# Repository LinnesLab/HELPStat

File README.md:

# HELPStat
Repository for our Handheld, EIS-Enabled, Low-cost and Portable (HELP) Potentiostat.

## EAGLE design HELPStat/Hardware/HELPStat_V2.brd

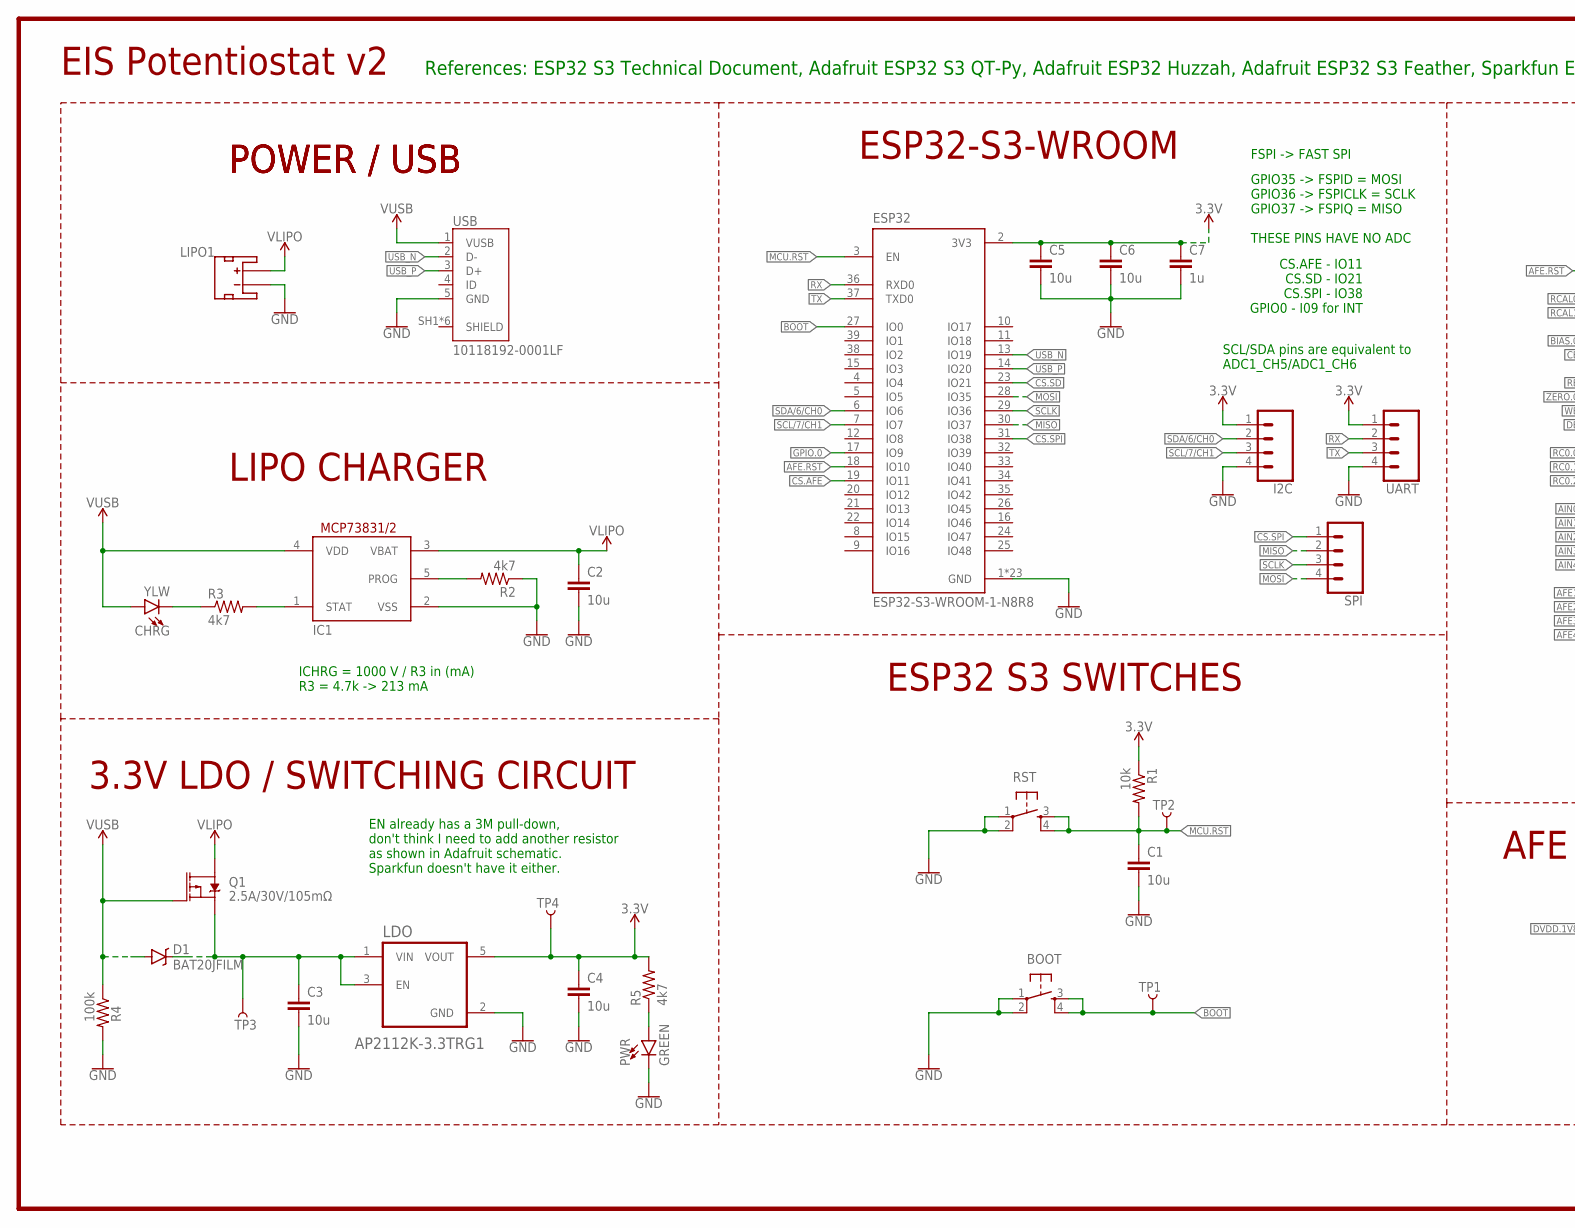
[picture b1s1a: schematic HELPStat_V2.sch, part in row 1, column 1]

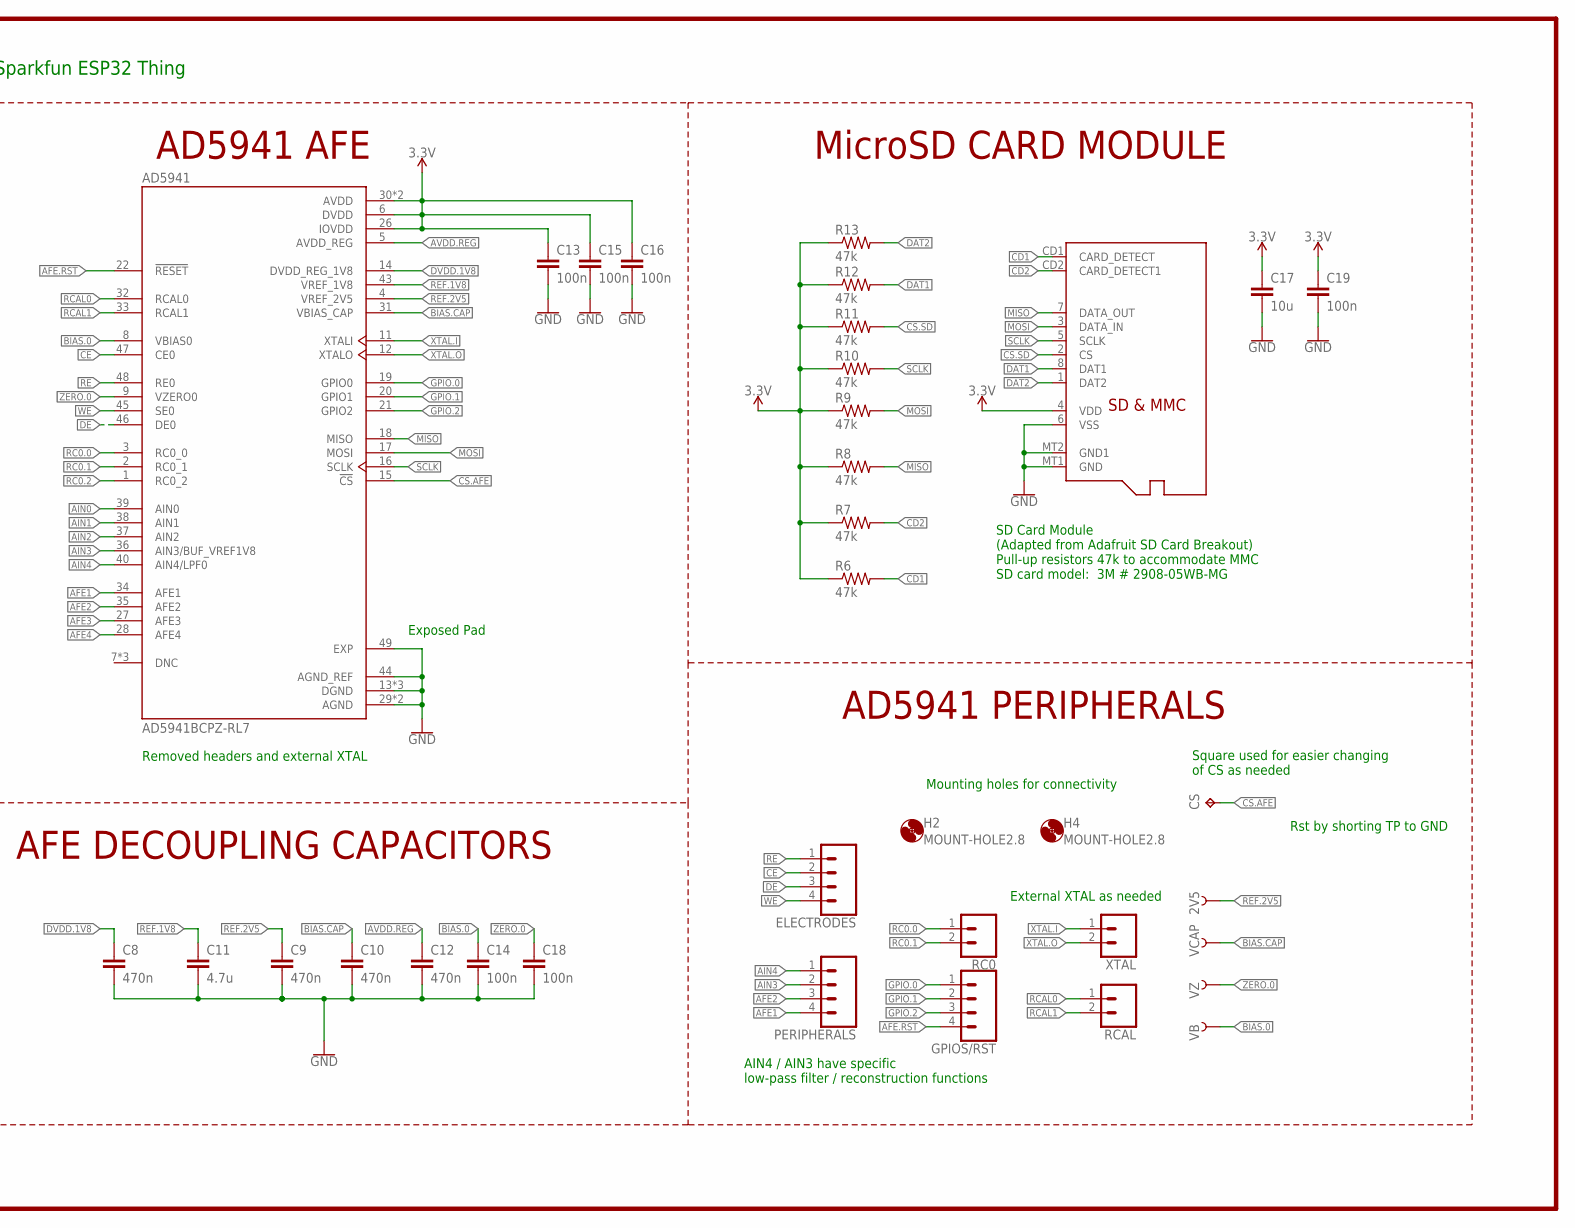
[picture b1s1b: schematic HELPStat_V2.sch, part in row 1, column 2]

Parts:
2V5: TEST-POINT3X5; PAD.03X.05
AD5941: AD5941BCPZ-RL7; QFN50P700X700X80-49N
BOOT: SPST-PTS830GG140; BUTTON-GULLWING
C1, C2, C3, C4, C5, C6, C17: 10u; C0402
C7: 1u; C0402
C8, C9, C10, C12: 470n; C0402
C11: 4.7u; C0402
C13, C14, C15, C16, C18, C19: 100n; C0402
CHRG: YLW; LED-0603
CS: TPTP20SQ; TP20SQ
D1: BAT20JFILM; SOD-323
ELECTRODES: CONN_04; 1X04
ESP32: ESP32-S3-WROOM-1-N8R8; XCVR_ESP32S3WROOM1N8R8
GPIOS/RST: CONN_041.27MM; 1X04_1.27MM
H2, H4: MOUNT-HOLE2.8; 2,8
I2C: CONN_04; 1X04
IC1: MCP73831/OT; SOT23-5L
LDO: AP2112K-3.3TRG1; SOT95P285X140-5N
LIPO1: JST_2MM_MALE; JST-2-SMD
PERIPHERALS: CONN_041.27MM; 1X04_1.27MM
PWR: GREEN; LED-0603
Q1: 2.5A/30V/105mΩ; SOT23-3
R1: 10k; R0402
R2, R3, R5: 4k7; R0402
R4: 100k; R0603
R6, R7, R8, R9, R10, R11, R12, R13: 47k; R0402
RC0: CONN_02.50MIL; 1X02_1.27MM
RCAL: CONN_02; 1X02
RST: SPST-PTS830GG140; BUTTON-GULLWING
SDCARD: MICROSD
SPI: CONN_04; 1X04
TP1, TP2, TP3, TP4: TEST-POINT3X5; PAD.03X.05
UART: CONN_04; 1X04
USB: 10118192-0001LF; AMPHENOL_10118192-0001LF
VB: TEST-POINT3X5; PAD.03X.05
VCAP: TEST-POINT3X5; PAD.03X.05
VZ: TEST-POINT3X5; PAD.03X.05
XTAL: CONN_02.50MIL; 1X02_1.27MM

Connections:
3.3V: AD5941.6 (DVDD), AD5941.26 (IOVDD), AD5941.30 (AVDD), AD5941.41 (AVDD), C4.1, C5.1, C6.1, C7.1, C13.1, C15.1, C16.1, C17.1, C19.1, ESP32.2 (3V3), I2C.1, LDO.5 (VOUT), R1.1, R5.2, R6.1, R7.1, R8.1, R9.1, R10.1, R11.1, R12.1, R13.1, SDCARD.4 (VDD), TP4.P$1, UART.1
AFE1: AD5941.34 (AFE1), PERIPHERALS.4
AFE2: AD5941.35 (AFE2), PERIPHERALS.3
AFE3: AD5941.27 (AFE3)
AFE4: AD5941.28 (AFE4)
AFE.RST: AD5941.22 (!RESET), ESP32.18 (IO10), GPIOS/RST.4
AIN0: AD5941.39 (AIN0)
AIN1: AD5941.38 (AIN1)
AIN2: AD5941.37 (AIN2)
AIN3: AD5941.36 (AIN3/BUF_VREF1V8), PERIPHERALS.2
AIN4: AD5941.40 (AIN4/LPF0), PERIPHERALS.1
AVDD.REG: AD5941.5 (AVDD_REG), C12.1
BIAS.0: AD5941.8 (VBIAS0), C14.1, VB.P$1
BIAS.CAP: AD5941.31 (VBIAS_CAP), C10.1, VCAP.P$1
BOOT: BOOT.3, BOOT.4, ESP32.27 (IO0), TP1.P$1
CD1: R6.2, SDCARD.CD1 (CARD_DETECT)
CD2: R7.2, SDCARD.CD2 (CARD_DETECT1)
CE: AD5941.47 (CE0), ELECTRODES.2
CS.AFE: AD5941.15 (!CS), CS.TP, ESP32.19 (IO11)
CS.SD: ESP32.23 (IO21), R11.2, SDCARD.2 (CS)
CS.SPI: ESP32.31 (IO38), SPI.1
DAT1: R12.2, SDCARD.8 (DAT1)
DAT2: R13.2, SDCARD.1 (DAT2)
DE: AD5941.46 (DE0), ELECTRODES.3
DVDD.1V8: AD5941.14 (DVDD_REG_1V8), C8.1
GND: AD5941.13 (DGND), AD5941.23 (DGND), AD5941.25 (DGND), AD5941.29 (AGND), AD5941.42 (AGND), AD5941.44 (AGND_REF), AD5941.49 (EXP), BOOT.1, BOOT.2, C1.2, C2.2, C3.2, C4.2, C5.2, C6.2, C7.2, C8.2, C9.2, C10.2, C11.2, C12.2, C13.2, C14.2, C15.2, C16.2, C17.2, C18.2, C19.2, ESP32.1 (GND), ESP32.40 (GND), ESP32.41_1 (GND), ESP32.41_2 (GND), ESP32.41_3 (GND), ESP32.41_4 (GND), ESP32.41_5 (GND), ESP32.41_6 (GND), ESP32.41_7 (GND), ESP32.41_8 (GND), ESP32.41_9 (GND), ESP32.41_10 (GND), ESP32.41_11 (GND), ESP32.41_12 (GND), ESP32.41_13 (GND), ESP32.41_14 (GND), ESP32.41_15 (GND), ESP32.41_16 (GND), ESP32.41_17 (GND), ESP32.41_18 (GND), ESP32.41_19 (GND), ESP32.41_20 (GND), ESP32.41_21 (GND), I2C.4, IC1.2 (VSS), LDO.2 (GND), LIPO1.1 (-), PWR.C, R2.1, R4.2, RST.1, RST.2, SDCARD.6 (VSS), SDCARD.MT1 (GND), SDCARD.MT2 (GND1), UART.4, USB.5 (GND)
GPIO.0: AD5941.19 (GPIO0), ESP32.17 (IO9), GPIOS/RST.1
GPIO.1: AD5941.20 (GPIO1), GPIOS/RST.2
GPIO.2: AD5941.21 (GPIO2), GPIOS/RST.3
MCU.RST: C1.1, ESP32.3 (EN), R1.2, RST.3, RST.4, TP2.P$1
MISO: AD5941.18 (MISO), ESP32.30 (IO37), R8.2, SDCARD.7 (DATA_OUT), SPI.2
MOSI: AD5941.17 (MOSI), ESP32.28 (IO35), R9.2, SDCARD.3 (DATA_IN), SPI.4
unnamed: CHRG.C, R3.1
unnamed: IC1.1 (STAT), R3.2
unnamed: IC1.5 (PROG), R2.2
unnamed: PWR.A, R5.1
unnamed: C3.1, D1.C, LDO.1 (VIN), LDO.3 (EN), Q1.2 (S), TP3.P$1
RC0.0: AD5941.3 (RC0_0), RC0.1
RC0.1: AD5941.2 (RC0_1), RC0.2
RC0.2: AD5941.1 (RC0_2)
RCAL0: AD5941.32 (RCAL0), RCAL.1
RCAL1: AD5941.33 (RCAL1), RCAL.2
RE: AD5941.48 (RE0), ELECTRODES.1
REF.1V8: AD5941.43 (VREF_1V8), C11.1
REF.2V5: 2V5.P$1, AD5941.4 (VREF_2V5), C9.1
RX: ESP32.36 (RXD0), UART.2
SCL/7/CH1: ESP32.7 (IO7), I2C.3
SCLK: AD5941.16 (SCLK), ESP32.29 (IO36), R10.2, SDCARD.5 (SCLK), SPI.3
SDA/6/CH0: ESP32.6 (IO6), I2C.2
TX: ESP32.37 (TXD0), UART.3
USB_N: ESP32.13 (IO19), USB.2 (D-)
USB_P: ESP32.14 (IO20), USB.3 (D+)
VLIPO: C2.1, IC1.3 (VBAT), LIPO1.2 (+), Q1.3 (D)
V_USB: CHRG.A, D1.A, IC1.4 (VDD), Q1.1 (G), R4.1, USB.1 (VUSB)
WE: AD5941.45 (SE0), ELECTRODES.4
XTAL.I: AD5941.11 (XTALI), XTAL.1
XTAL.O: AD5941.12 (XTALO), XTAL.2
ZERO.0: AD5941.9 (VZERO0), C18.1, VZ.P$1

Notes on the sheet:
ICHRG = 1000 V / R3 in (mA) R3 = 4.7k -> 213 mA
POWER / USB
LIPO CHARGER
3.3V LDO / SWITCHING CIRCUIT
ESP32 S3 SWITCHES
EIS Potentiostat v2
SCL/SDA pins are equivalent to ADC1_CH5/ADC1_CH6
References: ESP32 S3 Technical Document, Adafruit ESP32 S3 QT-Py, Adafruit ESP32 Huzzah, Adafruit ESP32 S3 Feather, Sparkfun ESP32 Thing
EN already has a 3M pull-down, don't think I need to add another resistor as shown in Adafruit schematic. Sparkfun doesn't have it either.
GPIO35 -> FSPID = MOSI GPIO36 -> FSPICLK = SCLK GPIO37 -> FSPIQ = MISO THESE PINS HAVE NO ADC
FSPI -> FAST SPI
ESP32-S3-WROOM
Exposed Pad
AFE DECOUPLING CAPACITORS
AD5941 AFE
Removed headers and external XTAL
CS.AFE - IO11 CS.SD - IO21 CS.SPI - IO38 GPIO0 - I09 for INT
SD Card Module (Adapted from Adafruit SD Card Breakout) Pull-up resistors 47k to accommodate MMC SD card model: 3M # 2908-05WB-MG
MicroSD CARD MODULE
AD5941 PERIPHERALS
Rst by shorting TP to GND
Square used for easier changing of CS as needed
AIN4 / AIN3 have specific low-pass filter / reconstruction functions
External XTAL as needed
Mounting holes for connectivity

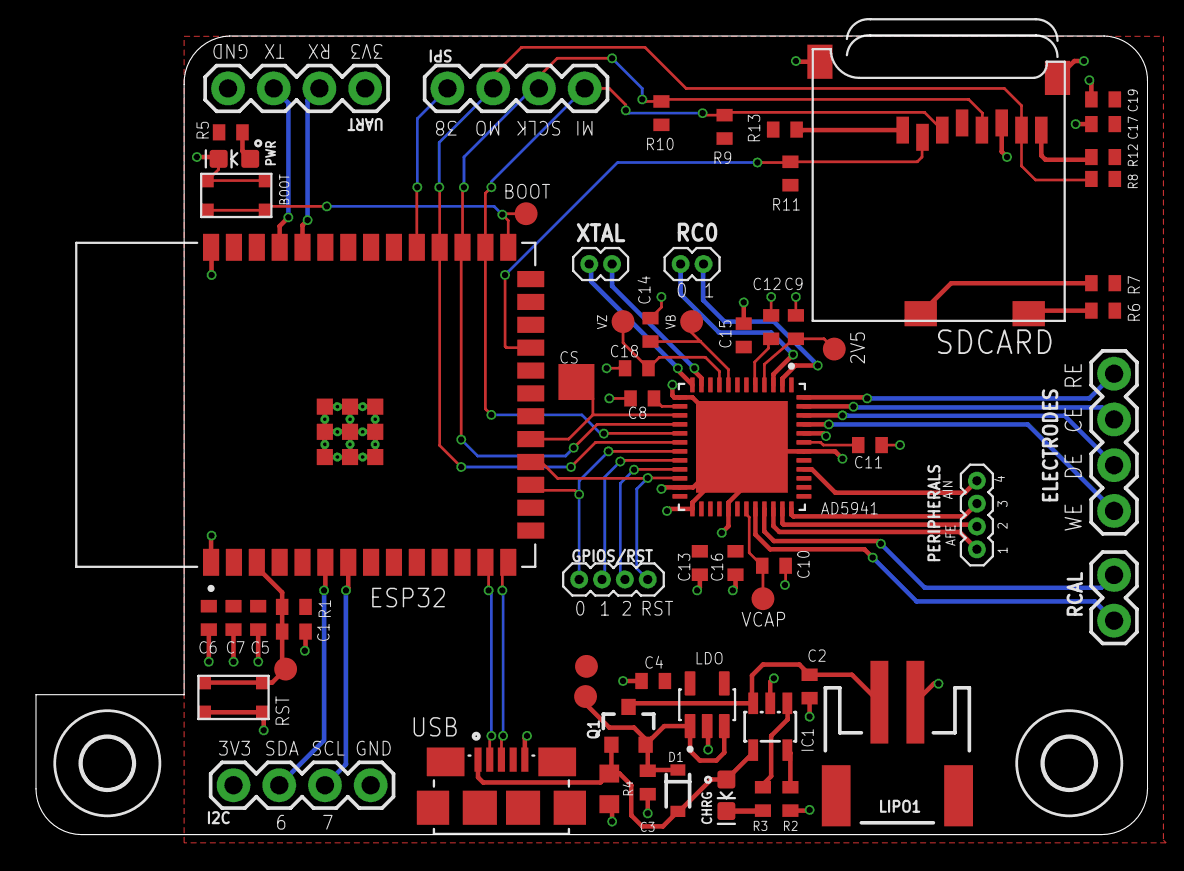
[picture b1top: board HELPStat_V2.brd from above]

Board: 2 copper layers, 61.8 x 44.4 mm, 65 parts (0 on the bottom side), 52 nets.

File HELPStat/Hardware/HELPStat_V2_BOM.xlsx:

@LinnesLab ESP32-S3 Potentisotat Rev B |  |  |  |  |  |  |  |  |  |  | Total | 28.54
BOM # | Comment | Designator | Description | Mounting Type | Package | Manufacturer | Manufacturer Part Number | Supplier | Supplier Part Number | Price per unit | Quantity | Total
1 | ESP32-S3-WROOM-1-N8R8 | MCU | Bluetooth, WiFi 802.11b/g/n, Bluetooth v5.0 Transceiver Module 2.4GHz PCB Trace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 | SMD | 41-SMD Module | Espressif Systems | ESP32-S3-WROOM-1-N8R8 | Digi-Key | 1965-ESP32-S3-WROOM-1-N8R8CT-ND | 3.62 | 1 | 3.62
2 | 3.3V Regulator | LDO | Linear Voltage Regulator IC Positive Fixed 1 Output 600mA SOT-25 | SMD | SOT-25 | Diodes Incorporated | AP2112K-3.3TRG1 | Digi-Key | AP2112K-3.3TRG1DITR-ND | 0.35 | 1 | 0.35
3 | Micro USB | USB | USB - micro B USB 2.0 Receptacle Connector 5 Position Surface Mount, Right Angle | SMD | Flange, Horizontal | Amphenol FCI | 10118192-0001LF | Digi-Key | 609-4613-1-ND | 0.46 | 1 | 0.46
4 | PFET | Q1 | P-Channel 30 V 2.5A (Ta) 760mW (Ta) Surface Mount SOT-23-3 | SMD | SOT-23-3 | Diodes Incorporated | DMG2307LQ-7 | Digi-Key | 31-DMG2307LQ-7TR-ND | 0.37 | 1 | 0.37
5 | Schottky Diode | D1 | DIODE SCHOTTKY 23V 1A SOD323 | SMD | SOD-323 | STMicroelectronics | BAT20JFILM | Digi-Key | 497-3381-2-ND | 0.4 | 1 | 0.4
6 | Tiny Rectangular Button | RST, BOOT | Tactile Switch SPST-NO Top Actuated Surface Mount | SMD | Gull Wing | C&K Components | PTS830GM140 SMTR LFS | Digi-Key | CKN10587CT-ND | 0.67 | 2 | 1.34
7 | LiPo Charger / Monitor | IC1 | IC BATT CNTL LI-ION 1CEL SOT23-5 | SMD | SOT-23-5 | Microchip Technology | MCP73812T-420I/OT | Digi-Key | MCP73812T-420I/OTTR-ND | 0.73 | 1 | 0.73
8 | Green LED | PWR | Green 571nm LED Indication - Discrete 2V 0603 (1608 Metric) | SMD | 0603 | Lite-On Inc. | LTST-C191KGKT | Digi-Key | 160-1446-2-ND | 0.26 | 1 | 0.26
9 | Yellow LED | CHRG | Yellow 591nm LED Indication - Discrete 2.1V 0603 (1608 Metric) | SMD | 0603 | Lite-On Inc. | LTST-C190KSKT | Digi-Key | 160-1437-2-ND | 0.26 | 1 | 0.26
10 | 100k Resistor | R4 | 100 kOhms ±1% 0.1W, 1/10W Chip Resistor 0603 (1608 Metric) Automotive AEC-Q200 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 | SMD | 0603 | Panasonic Electronic Components | ERJ-3EKF1003V | Digi-Key | P100KHTR-ND | 0.1 | 1 | 0.1
11 | 47k Resistor | R6, R7, R8, R9, R10, R11, R12, R13 | 47 kOhms ±5% 0.1W, 1/10W Chip Resistor 0402 (1005 Metric) Automotive AEC-Q200 T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 | SMD | 0402 | Panasonic Electronic Components | ERJ-2GEJ473X | Digi-Key | P47KJTR-ND | 0.1 | 8 | 0.8
12 | 10k Resistor | R1 | 10 kOhms ±1% 0.1W, 1/10W Chip Resistor 0402 (1005 Metric) Automotive AEC-Q200 T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 | SMD | 0402 | Panasonic Electronic Components | ERJ-2RKF1002X | Digi-Key | P10.0KLTR-ND | 0.1 | 1 | 0.1
13 | 4.7k Resistor | R2, R3, R5 | 4.7 kOhms ±1% 0.1W, 1/10W Chip Resistor 0402 (1005 Metric) Automotive AEC-Q200 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 | SMD | 0402 | Panasonic Electronic Components | ERJ-2RKF4701X | Digi-Key | P4.70KLTR-ND | 0.1 | 3 | 0.30000000000000004
14 | 10uF Capacitor | C1, C2, C3, C4, C5, C6, C17 | 10 µF ±20% 10V Ceramic Capacitor X5R 0402 (1005 Metric) | SMD | 0402 | Murata Electronics | GRM155R61A106ME11D | Digi-Key | 490-GRM155R61A106ME11DTR-ND | 0.13 | 7 | 0.91
15 | 4.7uF Capacitor | C11 | 4.7 µF ±20% 10V Ceramic Capacitor X5R 0402 (1005 Metric) | SMD | 0402 | Samsung Electro-Mechanics | CL05A475MP5NRNC | Digi-Key | 1276-1482-2-ND | 0.1 | 1 | 0.1
16 | 1uF Capacitor | C7 | 1 µF ±10% 25V Ceramic Capacitor X5R 0402 (1005 Metric) | SMD | 0402 | Murata Electronics | GRM155R61E105KA12D | Digi-Key | 490-10017-2-ND | 0.1 | 1 | 0.1
17 | 0.47uF Capacitor | C8, C9, C10, C12 | 0.47 µF ±10% 25V Ceramic Capacitor X5R 0402 (1005 Metric) | SMD | 0402 | TDK Corporation | C1005X5R1E474K050BB | Digi-Key | 445-8020-2-ND | 0.12 | 4 | 0.48
18 | 0.1uF Capacitor | C13, C14, C15, C16, C18, C19 | 0.1 µF ±10% 25V Ceramic Capacitor X5R 0402 (1005 Metric) | SMD | 0402 | Samsung Electro-Mechanics | CL05A104KA5NNNC | Digi-Key | 1276-1043-2-ND | 0.1 | 6 | 0.60000000000000009
19 | AD5941 AFE | AD5941 | BIO-IMPEDANCE & ELECTROCHEMICAL | SMD | 48-Lead LFSCP | Analog Devices Inc. | AD5941BCPZ-RL7 | Digi-Key | 505-AD5941BCPZ-RL7TR-ND | 11.45 | 1 | 11.45
20 | MicroSD Card slot | SDCARD | 8 Position Card Connector Secure Digital - microSD™ Surface Mount, Right Angle 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 | SMD | SMD, Right angle | 3M | 2908-05WB-MG | Digi-Key | 3M5607TR-ND | 4.8600000000000003 | 1 | 4.8600000000000003
21 | JST Connector | LIPO1 | 2-pin, compact SMT JST Connector | SMD | SMD, Right angle | SparkFun | PRT-11641 | SparkFun | PRT-11641 | 0.95 | 1 | 0.95

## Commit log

2024-05-31 Add files via upload
    initial commit
2024-05-31 Updated to reflect HELPStat name
2024-06-05 clarified SD card nomenclature
2024-06-10 cleaned up comments
2024-06-11 added comments and fixed function inputs
2024-06-11 Introducing basic BLE Functionality
    Implemented BLE based on EIS-LevenbergMarquardtAlgorithm work (see organization GitHub repo).
    TO-DO:
    * Finalize other BLE settings
    * Testing w/ Randle's cells, EIS samples, etc.
2024-06-12 Finish Implementing BLE
    Finished implementing BLE.
    Able to adjust:
    * Rct Estimate
    * Rs Estimate
    * Start Frequency
    * End Frequency
2024-06-13 Moved BLE Functionality to HELPStat Library
    BLE functions moved to HELPStat library for cleanliness. Note that HELPStat::AD5940_TDD and HELPStat::runSweep now have two overloading functions: one that uses the private variables as configured by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
2024-06-13 More cleanup
    Enough said
2024-06-17 Initial Commit for Android App
    So far just setting up a layout
2024-06-18 Reworked layout into scroll view
    Allows user to see all adjustable settings while typing.
    TO-DO:
    * Implement BLE communication. Been following a YouTube series by Philipp Lackner for layout, will check out this video by him discussing Bluetooth (https://youtu.be/A41hkHoYu4M?si=V4J_ACV5qzqgYmnZ).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
    * Create a "logger" tab that mirrors the data displayed in the serial monitor.
    * Maybe look into MIT App Inventory as an alternative to Android Studio. This is more like Scratch than a traditional coding language, so may not be as beneficial for long-term management.
2024-06-18 Started (hopefully) implementing BLE
    Started following a tutorial at: https://punchthrough.com/android-ble-guide/. Found that his seems to be the "gold-standard" tutorial for setting up BLE on Android. Will also be referring to Android 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
2024-06-18 Check if Bluetooth Enabled
2024-06-19 Fixed bug w/ HELPStatLib
    Found a bug in the HELPStatLib that prevented the push button to be used w/ the BLE start signal. Fixed this.
2024-06-19 BLE Functionality for Each Sweep
    Firmware now sends Index, Frequency, Zreal, and Zimag for every measurement. Also added the Excel sheet listing each UUID, what parameter is associated with it, and what BLE characteristics are used 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
2024-06-19 Debugging the BLE Field Data
    Found that sending data after each sweep caused faulty measurements. Instead implemented this into the transmit_resistors function. Will have to continue testing tomorrow, but so far, it appears to s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
2024-06-20 Bug Fix, Send Frequency, Real Impedence, and Imaginary Impedence Data
    Fixed the bug where sending data after each sweep messed w/ potentiostat timing and caused invalid measurements. Instead, send all impedence and frequency samples at the very end in the transmit_resi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
    TO-DO:
    * Delete the BLE characteristic for index. This is not used nor needs to be present for the Android app.
    * Work w/ BLE_settings() function to deal w/ push button.
2024-06-20 Started Implementing XY Plot for Zreal/imag data
    Since still waiting for access to circuits lab for current draw test and still waiting on Android for BLE testing, decided to deal with data visualization. Managed to get project to use the androidpl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
2024-06-20 redrawNyquist
    Wrote a function called redrawNyquist. When called, it clears the graph and draws a new one based off current Zreal/Zimag values. Once BLE is working, this will be called twice:
    (1) when the start button is clicked. This just clears Zreal and Zimag, making the graph a clear plot.
    (2) when all of the BLE data is received. This will then draw the Nyquist plot for the most recent sample.
    NOTE: I am electing to clear at the beginning of a sample so that the user can more easily tell when a sample is running (clear) vs when a sample is finished (semicircle).
2024-06-21 Settings Page
    Finally incorporated ability to open and close settings from home, rather than those being two unconnected layouts.
2024-06-21 Bluetooth Permissions
    Android App now asks user to enable BLE and other permissions when starting the app.
    NOTE: For some reason, if you turn off bluetooth AFTER opening the app, it never prompts you to turn bluetooth back on.
2024-06-21 BLE Scanning
    Now able to scan for a BLE device.
2024-06-21 BLE Scanning and Display
    Start & stop a scan, display results of scan to user. Added a filter that only looks for devices with name "HELPStat" to filter out any other device.
2024-06-24 Able to Connect
    Can now connect to HELPStat and discover all services and characteristics. Struggling to get it to actually write.
2024-06-24 Start Signal
    Can now signal the HELPStat PCB to start running a sample. Tested to ensure that we can run repeated samples w/o resetting the device.
2024-06-24 Update Settings
    Can somewhat update settings. Due to a few timing issues, a few values don't always get updated.
    BUG -> if you go home and reload the settings page, it all resets to default values instead of storing previous val.
2024-06-24 IDE Issue
    Had to delete from PC and pull from GitHub. Some setting in the IDE got messed up, eventually fixed it by deleting the entire build folder and letting AndroidStudio rebuild.
2024-06-24 Apply Each Setting Individual
    Original wanted to have all settings be adjusted at the same time. Unfortunately, this did not work due to timing issues (every now and then, one setting would not be adjusted while the others were).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
    TO-DO:
    * Configure notifications to read results (perhaps just have it save values to an object?
    * Adjust settings page. Maybe have the settings be blank on default?
2024-06-24 Receive and Save Real, Imag, and Freq Data
    Once received, able to save real, imag, and freq data to lists. Issue is that the display does not automatically update, so although these values get updated, the user is not shown that. Will be trou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
2024-06-25 Fully Functional Prototype for Android App
    Android App is now fully functional. On startup, user loads an empty Nyquist plot.
    First, user must connect to the HELPStat PCB. This is done by: (1) hitting "Start BLE Scan", (2) wait until "HELPStat" appears, (3) hit "Stop BLE Scan", and (4) hitting "HELPStat."
    Once connected, the user can hit "Settings" to change settings. Typing a value into a textfield and then hitting the corresponding "Apply" button will update the corresponding setting. To exit settin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
    Once ready, the user can hit "Start" to start a sample. Once the sample is complete, the values will display on the screen.
    TO-DO:
    * Modify the BLE Scan / Connec
2024-06-26 Semi-AutoConnect for App
    On startup, if user clicks on "Connect", the device will automatically start & stop BLE scan before connecting to HELPStat. In previous versions, this was a 3-step process.
    Tried to have the app immediately connect on startup, but causes the app to crash if BLE is not enabled (instead of prompting the user to turn on bluetooth).
    Also did some color changes to make it look better. I don't think it really worked.
2024-06-26 Update Settings
    Fixed bug where settings "revert" if user closes and reopens setting page even though no changes were made to the PCB.
    Found bug: if you close the app, you have to restart the device in order for BLE devices to connect again (not entirely sure why)
2024-06-27 Fixed Reconnection Bug
    Not entirely sure how, but fixed the bug that prevents the user from reconnecting to HELPStat if they close and reopen the device. Probably an issue with the teardownConnection making it impossible t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
2024-06-27 App Formatting
    Managed to adjust scaling on y-labels so that the numbers aren't cropped off by screen. Also added a plot of the fitted semicircle for comparison (albeit non-smooth/interpolated).
2024-06-27 Draw Fit Line
    App uses Rct and Rs to draw the semicircular fit. Did some adjustments making list a mutableList and replacing NaNs w/ 0 to ensure data plots multiple times. (Will continue testing).
2024-06-28 Bug Fixes, Bode Plot, Axis Titles
    * Fixed bug where app sometimes crashes when trying to redraw
    Found that app might try to refresh graph while receiving data, causing size mismatch error.
    * Adjusted the firmware library to also transmit the phase measurements.
    * Added functionality in app to receive the transmitted phase measurements and plot against log(f).
    * Added axis titles and managed to adjust positionings.
2024-06-28 Excel Document w/ UUIDs
    Update
2024-07-01 "Error" Alert, Switched from Rads to Degs
    * "Error" Alert -> Noticed that if the estimate for Rct/Rs was too far off, the fitting algorithm would not calculate a value. To compensate for this, added an error box that would say tell the user 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
    * Switched the phase diagram from rads to degs.
    * Minor clean-up of code.
2024-07-01 Test w/ APK
    Trying to test if able to install from APK download
2024-07-01 Bug Fix, Release File
    * Bug fix in redrawNyquist
    * Added release file (APK) for easy download and installation
2024-07-01 Minor plot adjustments
2024-07-01 Bug Fix
    Was subtracting 180* instead of 360* from phase errors.
2024-07-02 Added Magnitude
    Updated firmware to transmit magnitude data
    Updated software to receive and display magnitude data
    Added some formatting to fix origin at (0,0) for Nyquist plot
    Formatting to have x-axis tick marks for Bode plots to be 1.0 (for decades)
    Set y-axis boundary of 0 for Bode magnitude plot.
    Updated APK release file.
2024-07-03 Minor Clean-up of .ino file, adding licenses
2024-07-12 Button Bug Fix
    Fixed bug where HELPStat would start running samples before being told to by button or BLE.
    Also, moved all curly braces in code to be after function declaration for consistency.
2025-04-09 Update for esp32 v3.2 Library
    Arduino Library Manager upgraded ESP32 library to v3.2. Changed how String datatype was used. Updated to allow BLE functionality w/ updated firmware.
    TODO: Fix issue w/ SD card not mounting.
2026-06-10 Working on branching to a PlatformIO implementation
